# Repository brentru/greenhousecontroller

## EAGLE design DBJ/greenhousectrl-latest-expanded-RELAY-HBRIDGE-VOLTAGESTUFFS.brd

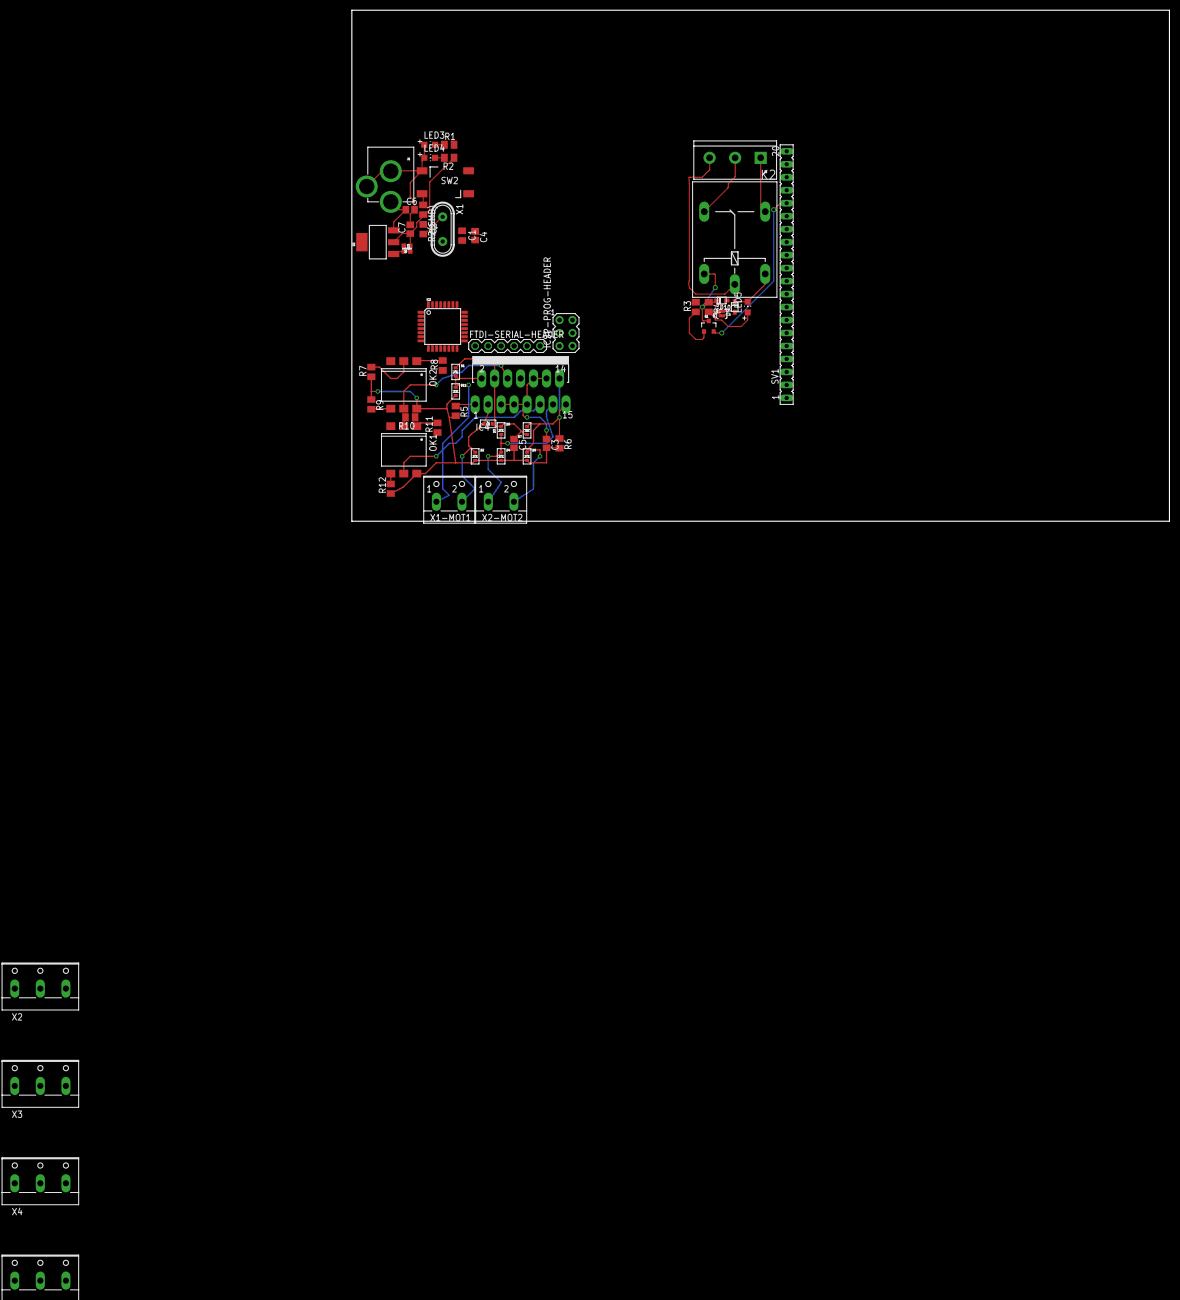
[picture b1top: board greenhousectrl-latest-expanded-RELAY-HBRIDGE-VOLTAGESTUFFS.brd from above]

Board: 2 copper layers, 160.0 x 100.0 mm, 56 parts (0 on the bottom side), 44 nets.

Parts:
C1, C2: C0805
C3, C5: 1.0uF; C0805
C4, C6, C7: 0.1uF; C0805
D1, D2, D3, D4, D5, D6, D7, D11: SOD-523
D9: 1N4148; SOD-323F
D10: Zener; SOD-323F
FTDI-SERIAL-HEADER: HEADER-06X1-MALE; 06X1-PTH
IC1: ATMEGA168TQFP-08; TQFP32-08
IC4: L298; MULTIWATT-15
ICSP-PROG-HEADER: AVRISP-6; AVRISP
J1: POWER_JACKPTH; POWER_JACK_PTH
J3: SCREWTERMINAL-5MM-3
JP1: JUMPER-PAD-2-NOYES_SILK; PAD-JUMPER-2-NO_YES_SILK
K2: G5LE
LED3, LED4, LED5: CHIP-LED0805
OK1, OK2: 4N27SM; DIL6-SMD
Q1: MMBT2222A; SOT23-3
R1, R2, R2(SMD), R5, R6, R7, R8, R9, R10, R11, R12: M0805
R3, R4: 1K; M0805
R13, R14: 0402-RES
SV1: FE20
SW2: MOMENTARYBUTTON; SPST_NO_SMD
U2: V_REG_317SMD; SOT223
X1: CRYSTALS-NOGND-HC49; HC49
X1-MOT1, X2-MOT2: W237-102
X2, X3, X4, X5: W237-103

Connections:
+5V: C3.1, C7.1, FTDI-SERIAL-HEADER.3, IC1.4, IC1.6, IC1.18, IC4.5, IC4.7, IC4.9, IC4.10, IC4.12, ICSP-PROG-HEADER.2, R2.1, R2(SMD).2, R14.2, SV1.2, SV1.15, U2.2, X2.2, X3.2, X4.2, X5.2
+12V: C5.1, C6.1, D1.K, D3.K, D5.K, D7.K, IC4.4, J1.PWR, U2.3
COIL: D10.C, JP1.1, K2.2, Q1.3, R4.1
COMMON: J3.3, K2.P
DIODENODE: D9.A, D10.A, JP1.2
DTR: C4.1, FTDI-SERIAL-HEADER.6
ENA: IC4.6, OK2.5
ENB: IC4.11, OK1.5
GND: C1.1, C2.1, C3.2, C5.2, C6.2, C7.2, D2.A, D4.A, D6.A, D11.A, FTDI-SERIAL-HEADER.1, IC1.3, IC1.5, IC1.21, IC4.8, ICSP-PROG-HEADER.6, J1.GND, J1.GNDBREAK, LED3.A, LED4.A, OK1.6, OK2.6, Q1.2, R5.2, R6.2, R7.1, R9.1, R10.1, R12.1, R13.1, SV1.1, SV1.3, SV1.16, SW2.4, X2.1, X3.1, X4.3, X5.3
MISO: IC1.16, ICSP-PROG-HEADER.1, SV1.13
MOSI: IC1.15, ICSP-PROG-HEADER.4, SV1.12
unnamed: OK2.1, R8.2
unnamed: LED4.C, R2.2
unnamed: LED5.A, R4.2
unnamed: OK2.2, R7.2
unnamed: OK2.4, R9.2
unnamed: Q1.1, R3.1
unnamed: R13.2, R14.1, U2.1
unnamed: OK1.1, R11.2
unnamed: OK1.2, R10.2
unnamed: LED3.C, R1.1
unnamed: C1.2, IC1.7, X1.2
unnamed: C2.2, IC1.8, X1.1
unnamed: OK1.4, R12.2
NC: J3.1, K2.S
NO: J3.2, K2.O
OUT1: D1.A, D11.K, IC4.2, X1-MOT1.1
OUT2: D2.K, D3.A, IC4.3, X1-MOT1.2
OUT3: D4.K, D5.A, IC4.13, X2-MOT2.1
OUT4: D6.K, D7.A, IC4.14, X2-MOT2.2
PB0: IC1.12, R3.2
PC0: IC1.23, X2.3
PC1: IC1.24, X3.3
PC2: IC1.25, X4.1
PC3: IC1.26, X5.1
PD4: IC1.2, R8.1
PD5: IC1.9, R11.1
RST: C4.2, IC1.29, ICSP-PROG-HEADER.5, R2(SMD).1, SW2.2
RX: FTDI-SERIAL-HEADER.5, IC1.30
SCK: IC1.17, ICSP-PROG-HEADER.3, R1.2, SV1.14
SEN_A: IC4.1, R5.1
SEN_B: IC4.15, R6.1
TX: FTDI-SERIAL-HEADER.4, IC1.31
VCC: D9.C, K2.1, LED5.C

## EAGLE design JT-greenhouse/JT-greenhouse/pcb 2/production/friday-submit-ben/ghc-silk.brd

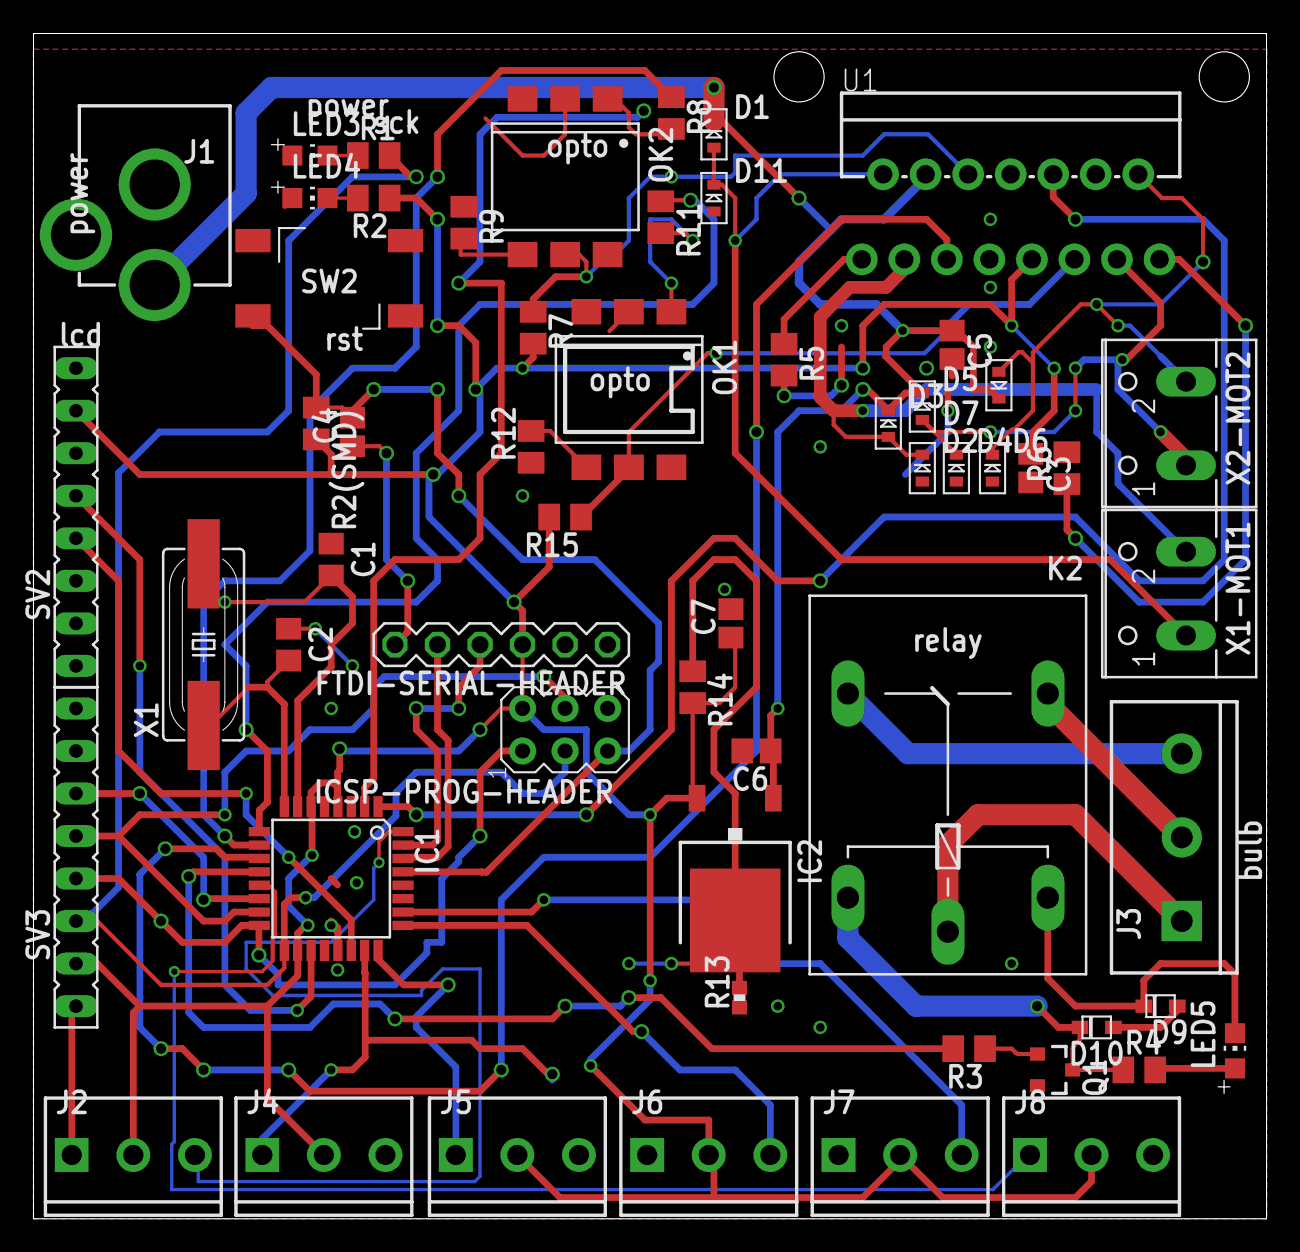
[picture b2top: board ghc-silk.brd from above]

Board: 2 copper layers, 73.6 x 70.8 mm, 58 parts (0 on the bottom side), 49 nets.

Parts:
C1, C2: 20pF; C0805
C3, C5: 1.0uF; C0805
C4, C6, C7: 0.1uF; C0805
D1, D2, D3, D4, D5, D6, D7, D11: SOD-523
D9: 1N4148; SOD-323F
D10: Zener; SOD-323F
FTDI-SERIAL-HEADER: HEADER-06X1-MALE; 06X1-PTH
IC1: ATMEGA168TQFP-08; TQFP32-08
IC2: 7805DT; TO252
ICSP-PROG-HEADER: AVRISP-6; AVRISP
J1: POWER_JACKPTH; POWER_JACK_PTH
J2, J4, J5, J6, J7, J8: SCREWTERMINAL-3.5MM-3_LOCK.007S
J3: SCREWTERMINAL-5MM-3
K2: G5LE
LED3, LED4, LED5: CHIP-LED0805
OK1, OK2: 4N27SM; DIL6-SMD
Q1: MMBT2222A; SOT23-3
R1, R2, R4: 150; M0805
R2(SMD), R5, R6: 10k; M0805
R3, R7, R9, R12, R14, R15: 1k; M0805
R8, R11: 240; M0805
R13: 3k; 0402-RES
SV2, SV3: FE08
SW2: MOMENTARYBUTTON; SPST_NO_SMD
U1: L298HEATSINK; MULTIWATT15_6400BGHEATSINK
X1: HC49UP
X1-MOT1, X2-MOT2: W237-102

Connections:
+5V: C3.1, C7.1, FTDI-SERIAL-HEADER.3, IC1.4, IC1.6, IC1.18, IC2.2, ICSP-PROG-HEADER.2, J2.2, J4.2, J5.2, J6.2, J7.2, J8.2, R2.1, R2(SMD).2, R7.2, R14.2, R15.2, SV2.7, SV3.2, U1.9
+12V: C5.1, C6.1, D1.K, D3.K, D5.K, D7.K, IC2.1, J1.PWR, U1.4
ADC6: IC1.19, SV2.5
ADC7: IC1.22, SV2.4
COIL: D10.C, K2.2, Q1.3, R4.1
COMMON: J3.1, K2.P
DIODENODE: D9.A, D10.A
DTR: C4.1, FTDI-SERIAL-HEADER.6
ENA: OK2.5, R7.1, U1.6
ENB: OK1.5, R15.1, U1.11
GND: C1.1, C2.1, C3.2, C5.2, C6.2, C7.2, D2.A, D4.A, D6.A, D11.A, FTDI-SERIAL-HEADER.1, IC1.3, IC1.5, IC1.21, ICSP-PROG-HEADER.6, J1.GND, J1.GNDBREAK, J2.1, J4.3, J5.3, J6.1, J7.1, J8.3, LED3.A, LED4.A, OK1.2, OK1.6, OK2.2, OK2.6, Q1.2, R5.2, R6.2, R9.1, R12.1, R13.1, SV2.6, SV2.8, SV3.1, SW2.4, U1.7, U1.8, U1.12
MISO: IC1.16, ICSP-PROG-HEADER.1, SV3.4
MOSI: IC1.15, ICSP-PROG-HEADER.4, SV3.5
unnamed: OK2.1, R8.2
unnamed: LED4.C, R2.2
unnamed: LED5.A, R4.2
unnamed: OK2.4, R9.2
unnamed: Q1.1, R3.1
unnamed: IC2.3, R13.2, R14.1
unnamed: OK1.1, R11.2
unnamed: LED3.C, R1.1
unnamed: C1.2, IC1.7, X1.2
unnamed: C2.2, IC1.8, X1.1
unnamed: OK1.4, R12.2
unnamed: R5.1, U1.1
unnamed: R6.1, U1.15
NC: J3.2, K2.S
NO: J3.3, K2.O
OUT1: D1.A, D11.K, U1.2, X1-MOT1.1
OUT2: D2.K, D3.A, U1.3, X1-MOT1.2
OUT3: D4.K, D5.A, U1.13, X2-MOT2.1
OUT4: D6.K, D7.A, U1.14, X2-MOT2.2
PB0: IC1.12, R3.2
PB1: IC1.13, J8.1
PB2: IC1.14, SV3.6
PC0: IC1.23, J4.1
PC1: IC1.24, J5.1
PC2: IC1.25, J6.3
PC3: IC1.26, J7.3
PD2: IC1.32, J2.3
PD3: IC1.1, U1.10
PD5: IC1.9, R11.1
PD6: IC1.10, R8.1
PD7: IC1.11, U1.5
RST: C4.2, IC1.29, ICSP-PROG-HEADER.5, R2(SMD).1, SW2.2
RX: FTDI-SERIAL-HEADER.5, IC1.30
SCK: IC1.17, ICSP-PROG-HEADER.3, R1.2, SV3.3
TX: FTDI-SERIAL-HEADER.4, IC1.31
VCC: D9.C, K2.1, LED5.C

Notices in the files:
parts and their libraries:
GeekAmmo: Licensing:Creative Commons ShareAlike 4.0 International - https://creativecommons.org/licenses/by-sa/4.0
